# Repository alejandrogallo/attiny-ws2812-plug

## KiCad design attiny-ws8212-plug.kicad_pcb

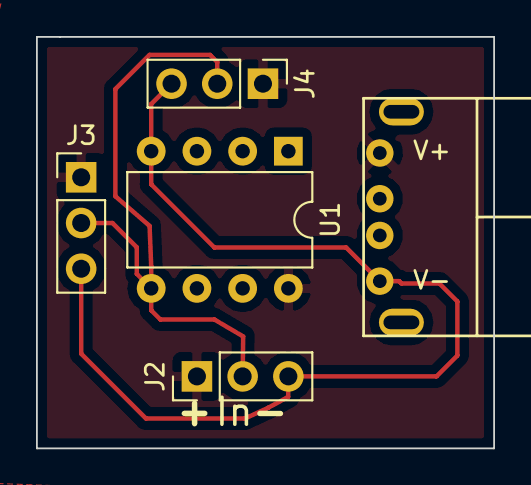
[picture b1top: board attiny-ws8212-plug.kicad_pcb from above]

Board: 2 copper layers, 25.4 x 22.9 mm, 5 parts (0 on the bottom side), 3 nets.

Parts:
J1: USB_A; USBA_Male_ebay
J2, J3, J4: WS2812; PinHeader_1x03_P2.54mm_Vertical
U1: ATtiny13-20PU; DIP-8_W7.62mm

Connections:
DataIn: J2.2, J3.2, J4.2, U1.5
GND: J1.4, J2.3, J3.3, J4.3, U1.4
VCC: J1.1, J2.1, J3.1, J4.1, U1.8

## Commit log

2020-03-09 Update schematics to 2.54mm of the pins
